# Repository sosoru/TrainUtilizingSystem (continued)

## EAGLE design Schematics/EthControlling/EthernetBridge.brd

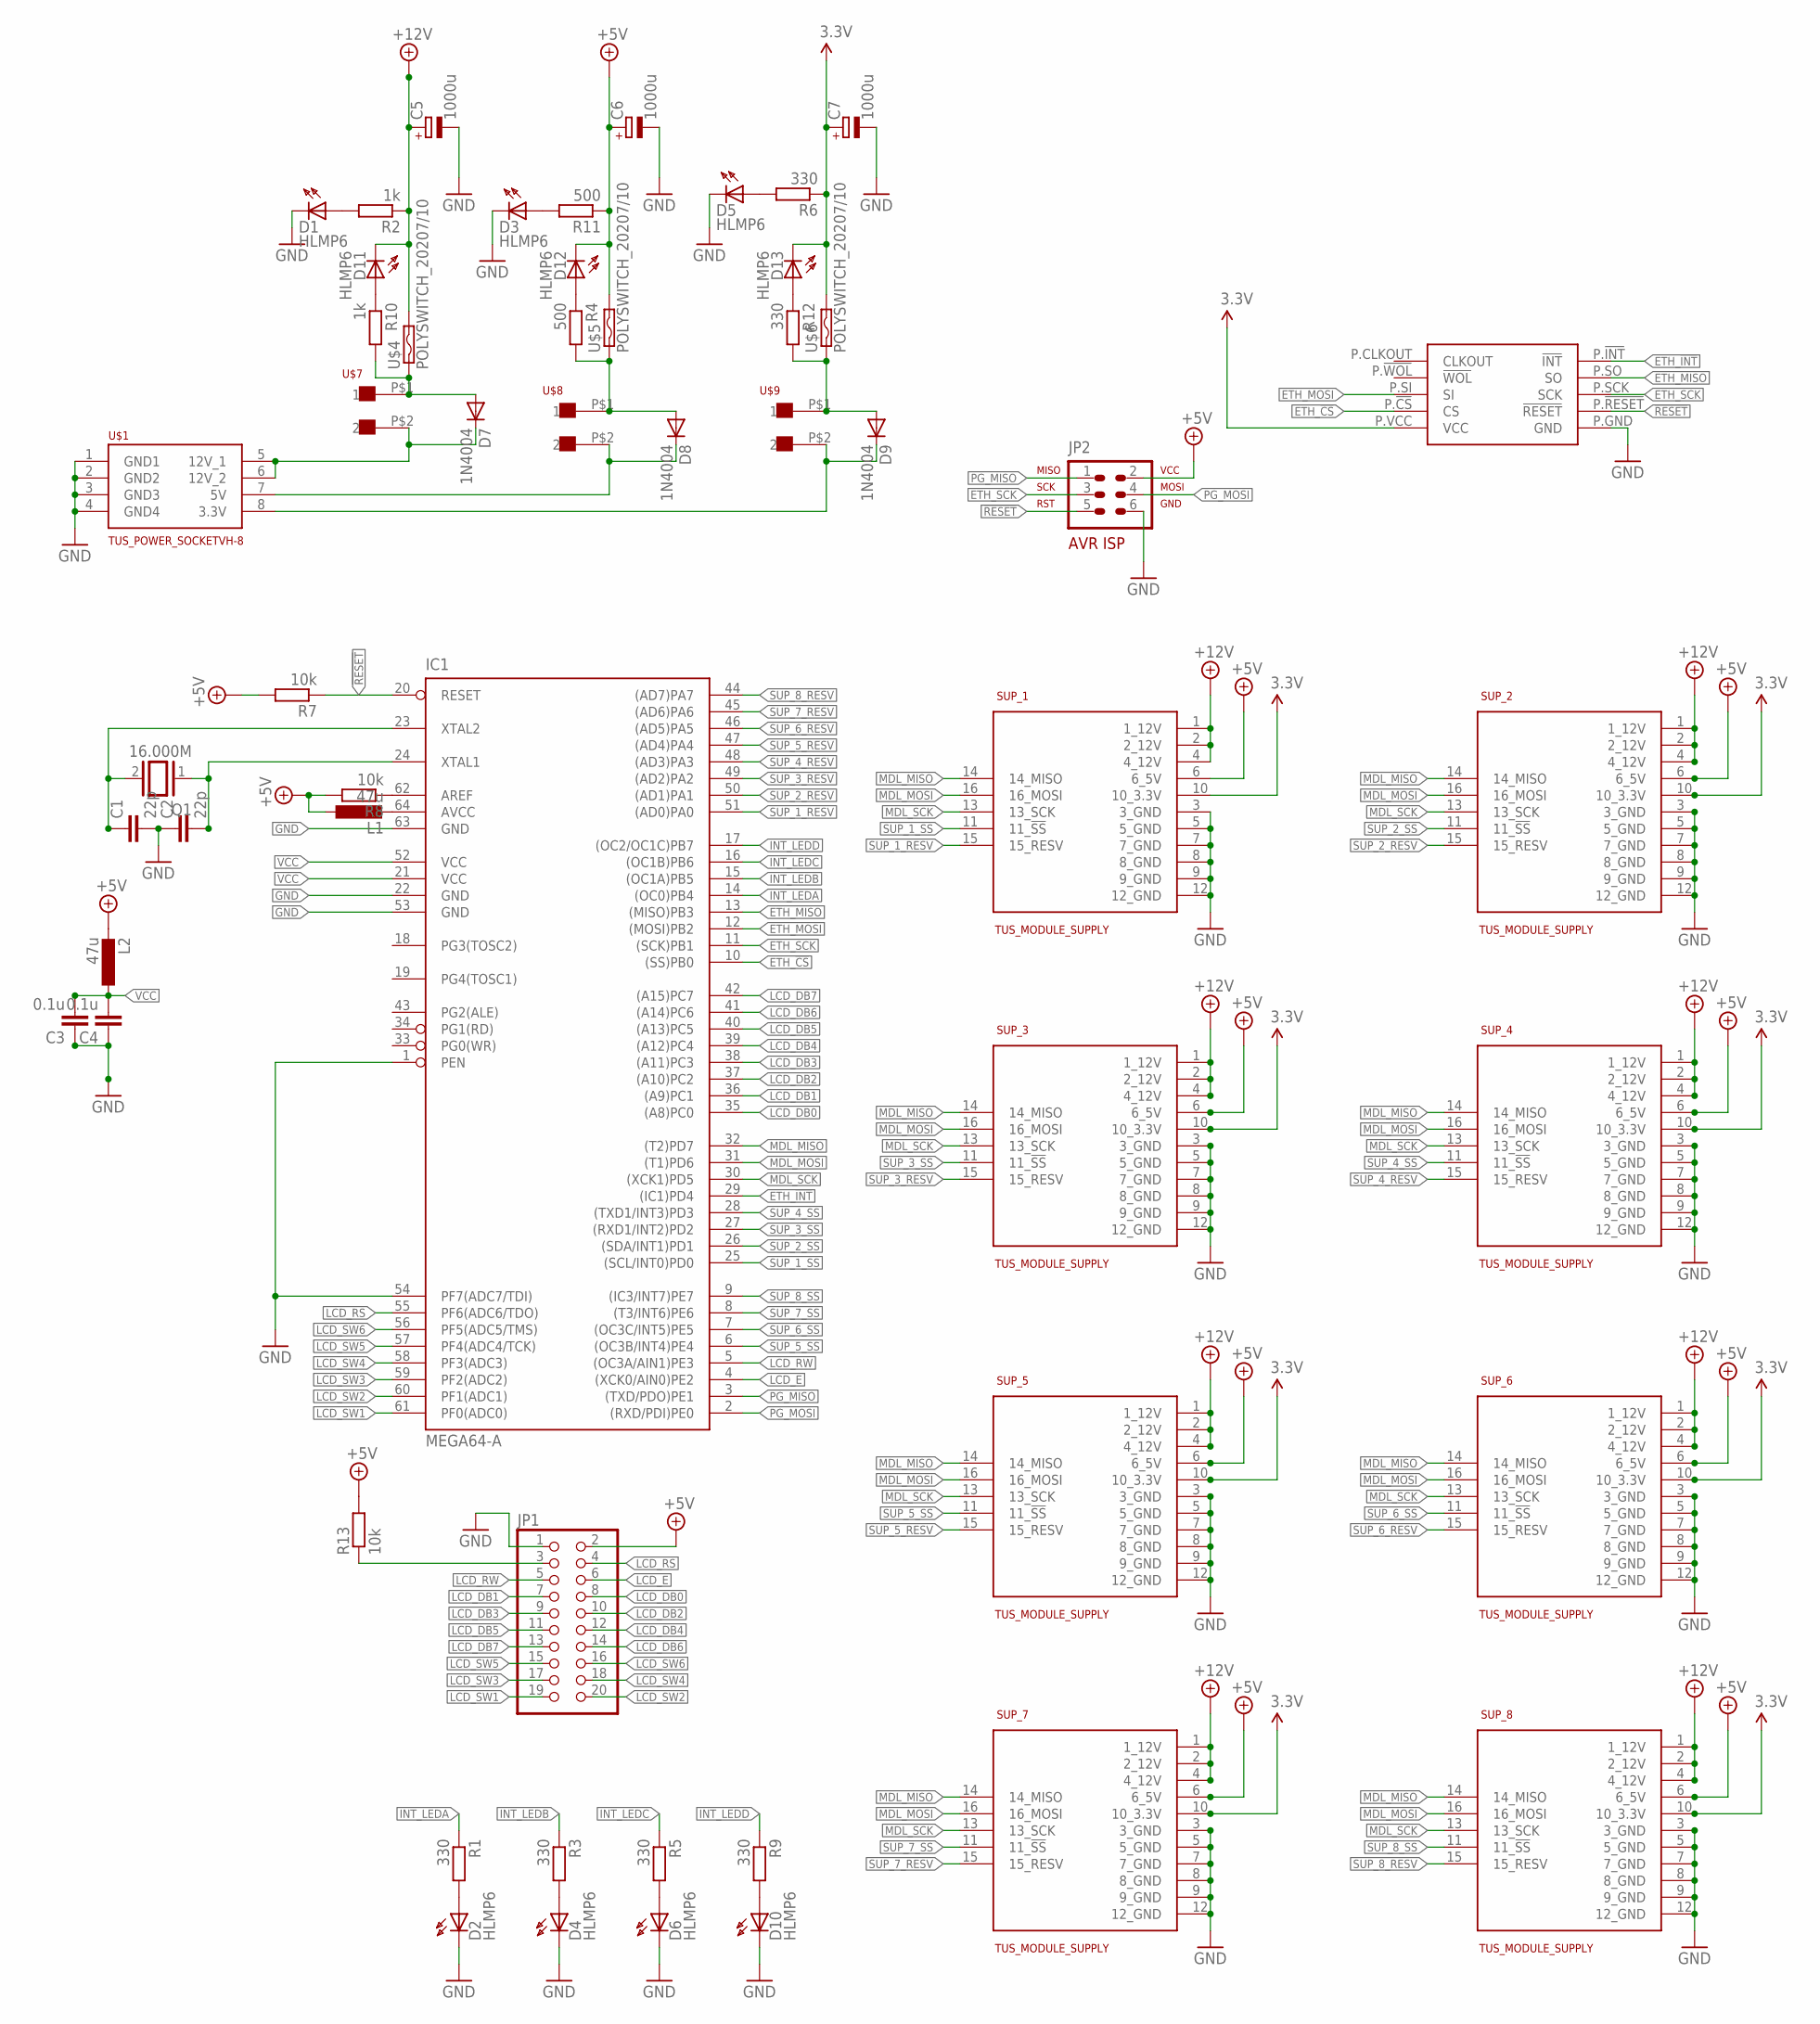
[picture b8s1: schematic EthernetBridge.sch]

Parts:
C1, C2: 22p; C2.5-3
C3, C4: 0.1u; C2.5-3
C5, C6, C7: 1000u; E5-10,5
D1, D2, D3, D4, D5, D6, D10, D11, D12, D13: HLMP6
D7, D8, D9: 1N4004; DO41-10
IC1: MEGA64-A; TQFP64
JP1: PINHD-2X10; 2X10
JP2: AVR-ISP-6VERT; AVR-ISP-6
L1, L2: 47u; 0204/7
Q1: 16.000M; QS
R1, R3, R5, R6, R9, R12: 330; 0204/7
R2, R10: 1k; 0204/7
R4, R11: 500; 0204/7
R7, R8, R13: 10k; 0204/7
SUP_1, SUP_2, SUP_3, SUP_4, SUP_5, SUP_6, SUP_7, SUP_8: TUS_MODULE_SUPPLY; 2X08
U$1: TUS_POWER_SOCKETVH-8; VH_8
U$2: AITENDO_ENC28J60
U$4, U$5, U$6: POLYSWITCH_20207/10; 0207/10
U$7, U$8, U$9: VH-2

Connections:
3.3V: C7.+, D13.K, R6.1, SUP_1.10 (10_3.3V), SUP_2.10 (10_3.3V), SUP_3.10 (10_3.3V), SUP_4.10 (10_3.3V), SUP_5.10 (10_3.3V), SUP_6.10 (10_3.3V), SUP_7.10 (10_3.3V), SUP_8.10 (10_3.3V), U$2.P.VCC (VCC), U$6.2
!RESET: IC1.20 (RESET), JP2.5, R7.1, U$2.P.!RESET (!RESET)
+5V: C6.+, D12.K, JP1.2, JP2.2, L1.1, L2.2, R7.2, R8.2, R11.1, R13.2, SUP_1.6 (6_5V), SUP_2.6 (6_5V), SUP_3.6 (6_5V), SUP_4.6 (6_5V), SUP_5.6 (6_5V), SUP_6.6 (6_5V), SUP_7.6 (6_5V), SUP_8.6 (6_5V), U$5.2
+12V: C5.+, D11.K, R2.1, SUP_1.1 (1_12V), SUP_1.2 (2_12V), SUP_1.4 (4_12V), SUP_2.1 (1_12V), SUP_2.2 (2_12V), SUP_2.4 (4_12V), SUP_3.1 (1_12V), SUP_3.2 (2_12V), SUP_3.4 (4_12V), SUP_4.1 (1_12V), SUP_4.2 (2_12V), SUP_4.4 (4_12V), SUP_5.1 (1_12V), SUP_5.2 (2_12V), SUP_5.4 (4_12V), SUP_6.1 (1_12V), SUP_6.2 (2_12V), SUP_6.4 (4_12V), SUP_7.1 (1_12V), SUP_7.2 (2_12V), SUP_7.4 (4_12V), SUP_8.1 (1_12V), SUP_8.2 (2_12V), SUP_8.4 (4_12V), U$4.2
ETH_!CS: IC1.10 ((SS)PB0), U$2.P.!CS (CS)
ETH_!INT: IC1.29 ((IC1)PD4), U$2.P.!INT (!INT)
ETH_MISO: IC1.13 ((MISO)PB3), U$2.P.SO (SO)
ETH_MOSI: IC1.12 ((MOSI)PB2), U$2.P.SI (SI)
ETH_SCK: IC1.11 ((SCK)PB1), JP2.3, U$2.P.SCK (SCK)
GND: C1.2, C2.1, C3.1, C4.1, C5.-, C6.-, C7.-, D1.K, D2.K, D3.K, D4.K, D5.K, D6.K, D10.K, IC1.1 (PEN), IC1.22 (GND), IC1.53 (GND), IC1.54 (PF7(ADC7/TDI)), IC1.63 (GND), JP1.1, JP2.6, SUP_1.3 (3_GND), SUP_1.5 (5_GND), SUP_1.7 (7_GND), SUP_1.8 (8_GND), SUP_1.9 (9_GND), SUP_1.12 (12_GND), SUP_2.3 (3_GND), SUP_2.5 (5_GND), SUP_2.7 (7_GND), SUP_2.8 (8_GND), SUP_2.9 (9_GND), SUP_2.12 (12_GND), SUP_3.3 (3_GND), SUP_3.5 (5_GND), SUP_3.7 (7_GND), SUP_3.8 (8_GND), SUP_3.9 (9_GND), SUP_3.12 (12_GND), SUP_4.3 (3_GND), SUP_4.5 (5_GND), SUP_4.7 (7_GND), SUP_4.8 (8_GND), SUP_4.9 (9_GND), SUP_4.12 (12_GND), SUP_5.3 (3_GND), SUP_5.5 (5_GND), SUP_5.7 (7_GND), SUP_5.8 (8_GND), SUP_5.9 (9_GND), SUP_5.12 (12_GND), SUP_6.3 (3_GND), SUP_6.5 (5_GND), SUP_6.7 (7_GND), SUP_6.8 (8_GND), SUP_6.9 (9_GND), SUP_6.12 (12_GND), SUP_7.3 (3_GND), SUP_7.5 (5_GND), SUP_7.7 (7_GND), SUP_7.8 (8_GND), SUP_7.9 (9_GND), SUP_7.12 (12_GND), SUP_8.3 (3_GND), SUP_8.5 (5_GND), SUP_8.7 (7_GND), SUP_8.8 (8_GND), SUP_8.9 (9_GND), SUP_8.12 (12_GND), U$1.1 (GND1), U$1.2 (GND2), U$1.3 (GND3), U$1.4 (GND4), U$2.P.GND (GND)
INT_LEDA: IC1.14 ((OC0)PB4), R1.1
INT_LEDB: IC1.15 ((OC1A)PB5), R3.1
INT_LEDC: IC1.16 ((OC1B)PB6), R5.1
INT_LEDD: IC1.17 ((OC2/OC1C)PB7), R9.1
LCD_DB0: IC1.35 ((A8)PC0), JP1.8
LCD_DB1: IC1.36 ((A9)PC1), JP1.7
LCD_DB2: IC1.37 ((A10)PC2), JP1.10
LCD_DB3: IC1.38 ((A11)PC3), JP1.9
LCD_DB4: IC1.39 ((A12)PC4), JP1.12
LCD_DB5: IC1.40 ((A13)PC5), JP1.11
LCD_DB6: IC1.41 ((A14)PC6), JP1.14
LCD_DB7: IC1.42 ((A15)PC7), JP1.13
LCD_E: IC1.4 ((XCK0/AIN0)PE2), JP1.6
LCD_RS: IC1.55 (PF6(ADC6/TDO)), JP1.4
LCD_RW: IC1.5 ((OC3A/AIN1)PE3), JP1.5
LCD_SW1: IC1.61 (PF0(ADC0)), JP1.19
LCD_SW2: IC1.60 (PF1(ADC1)), JP1.20
LCD_SW3: IC1.59 (PF2(ADC2)), JP1.17
LCD_SW4: IC1.58 (PF3(ADC3)), JP1.18
LCD_SW5: IC1.57 (PF4(ADC4/TCK)), JP1.15
LCD_SW6: IC1.56 (PF5(ADC5/TMS)), JP1.16
LCD_VO: JP1.3, R13.1
MDL_MISO: IC1.32 ((T2)PD7), SUP_1.14 (14_MISO), SUP_2.14 (14_MISO), SUP_3.14 (14_MISO), SUP_4.14 (14_MISO), SUP_5.14 (14_MISO), SUP_6.14 (14_MISO), SUP_7.14 (14_MISO), SUP_8.14 (14_MISO)
MDL_MOSI: IC1.31 ((T1)PD6), SUP_1.16 (16_MOSI), SUP_2.16 (16_MOSI), SUP_3.16 (16_MOSI), SUP_4.16 (16_MOSI), SUP_5.16 (16_MOSI), SUP_6.16 (16_MOSI), SUP_7.16 (16_MOSI), SUP_8.16 (16_MOSI)
MDL_SCK: IC1.30 ((XCK1)PD5), SUP_1.13 (13_SCK), SUP_2.13 (13_SCK), SUP_3.13 (13_SCK), SUP_4.13 (13_SCK), SUP_5.13 (13_SCK), SUP_6.13 (13_SCK), SUP_7.13 (13_SCK), SUP_8.13 (13_SCK)
unnamed: IC1.64 (AVCC), L1.2
unnamed: D1.A, R2.2
unnamed: D2.A, R1.2
unnamed: D4.A, R3.2
unnamed: D8.A, R4.2, U$5.1, U$8.P$1 (1)
unnamed: D9.C, U$1.8 (3.3V), U$9.P$2 (2)
unnamed: D6.A, R5.2
unnamed: D5.A, R6.2
unnamed: C2.2, IC1.24 (XTAL1), Q1.1
unnamed: D10.A, R9.2
unnamed: C1.1, IC1.23 (XTAL2), Q1.2
unnamed: IC1.62 (AREF), R8.1
unnamed: D7.A, R10.2, U$4.1, U$7.P$1 (1)
unnamed: D11.A, R10.1
unnamed: D3.A, R11.2
unnamed: D12.A, R4.1
unnamed: D13.A, R12.1
unnamed: D9.A, R12.2, U$6.1, U$9.P$1 (1)
unnamed: D7.C, U$1.5 (12V_1), U$1.6 (12V_2), U$7.P$2 (2)
unnamed: D8.C, U$1.7 (5V), U$8.P$2 (2)
PG_MISO: IC1.3 ((TXD/PDO)PE1), JP2.1
PG_MOSI: IC1.2 ((RXD/PDI)PE0), JP2.4
SUP_1_RESV: IC1.51 ((AD0)PA0), SUP_1.15 (15_RESV)
SUP_1_SS: IC1.25 ((SCL/INT0)PD0), SUP_1.11 (11_!SS)
SUP_2_RESV: IC1.50 ((AD1)PA1), SUP_2.15 (15_RESV)
SUP_2_SS: IC1.26 ((SDA/INT1)PD1), SUP_2.11 (11_!SS)
SUP_3_RESV: IC1.49 ((AD2)PA2), SUP_3.15 (15_RESV)
SUP_3_SS: IC1.27 ((RXD1/INT2)PD2), SUP_3.11 (11_!SS)
SUP_4_RESV: IC1.48 ((AD3)PA3), SUP_4.15 (15_RESV)
SUP_4_SS: IC1.28 ((TXD1/INT3)PD3), SUP_4.11 (11_!SS)
SUP_5_RESV: IC1.47 ((AD4)PA4), SUP_5.15 (15_RESV)
SUP_5_SS: IC1.6 ((OC3B/INT4)PE4), SUP_5.11 (11_!SS)
SUP_6_RESV: IC1.46 ((AD5)PA5), SUP_6.15 (15_RESV)
SUP_6_SS: IC1.7 ((OC3C/INT5)PE5), SUP_6.11 (11_!SS)
SUP_7_RESV: IC1.45 ((AD6)PA6), SUP_7.15 (15_RESV)
SUP_7_SS: IC1.8 ((T3/INT6)PE6), SUP_7.11 (11_!SS)
SUP_8_RESV: IC1.44 ((AD7)PA7), SUP_8.15 (15_RESV)
SUP_8_SS: IC1.9 ((IC3/INT7)PE7), SUP_8.11 (11_!SS)
VCC: C3.2, C4.2, IC1.21 (VCC), IC1.52 (VCC), L2.1

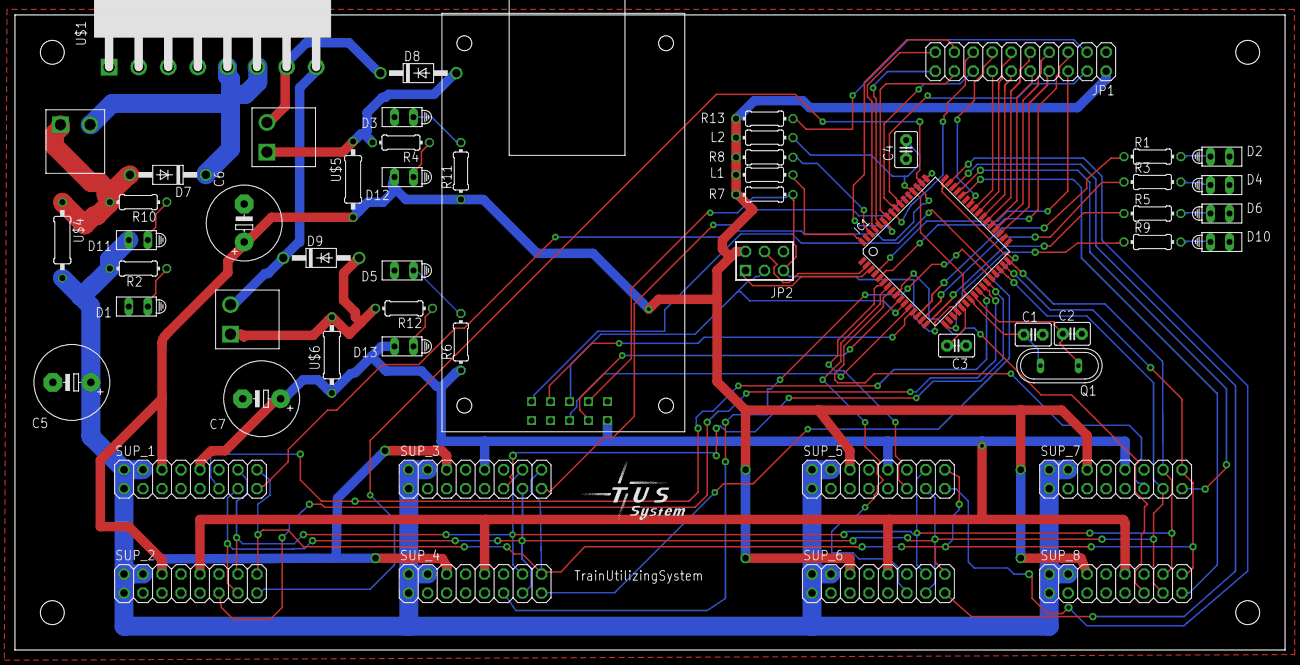
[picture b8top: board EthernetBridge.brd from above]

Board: 2 copper layers, 170.0 x 85.0 mm, 55 parts (0 on the bottom side), 74 nets.

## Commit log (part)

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2012-11-21 [autosave] TusSolution/DialogConsole/DialogConsole.cs
2012-11-21 [autosave] SensorLibrary/Packet/PacketIO/EthClient.cs
2012-11-21 [autosave] TestProject/TestProject.csproj
2012-11-21 [autosave] TestProject/RouteTest/UnitTest1.cs
2012-11-21 [autosave] TusSolution/DialogConsole/RouteGeneratorForTwelve.cs
2012-11-21 [autosave] TestProject/RouteTest/TwelveLayoutTest.cs
2012-11-21 [autosave] TusSolution/DialogConsole/DialogConsole.csproj
2012-11-21 [autosave] TusSolution/RouteLibrary/Base/Route.cs
2012-11-22 [autosave] TusSolution/RouteLibrary/Base/DeviceEffector.cs
2012-11-22 [autosave] TusSolution/RouteLibrary/Base/BlockSheet.cs
2012-11-22 [autosave] TusSolution/RouteLibrary/Base/Vehicle.cs
2012-11-23 [autosave] TestProject/RouteTest/StaLoopTest.cs
2012-11-23 [autosave] TestProject/EthClientTest.cs
2012-11-24 [autosave] SensorLibrary/Packet/PacketDatas/PacketBasis.cs
2012-11-24 [autosave] SensorLibrary/Packet/PacketControl/PacketServer.cs
2012-11-24 [autosave] TusSolution/DengoController/Program.cs
2012-11-24 [autosave] TusSolution/DengoController/DengoController.csproj
2012-11-27 [autosave] TusSolution/TusSolution.sln
2012-11-28 published for festival at 12/11/28
2012-11-28 [autosave] TestProject/app.config
2012-11-28 [autosave] TusSolution/DialogConsole/App.config
2012-11-28 [autosave] TusSolution/RouteLibrary/RouteLibrary.csproj
2012-11-30 [autosave] SensorLibrary/Packet/PacketIO/TusEthernetIO.cs
2012-12-01 [autosave] SensorLibrary/SensorLibrary.csproj
2012-12-23 [autosave] TestProject/ConsoleTest/SheetFactoryTest.cs
2012-12-23 [autosave] TusSolution/DialogConsole/Factory/SheetFactory.cs
2012-12-24 [autosave] TusSolution/DialogConsole/Factory/ServerFactory.cs
2012-12-25 [autosave] TusSolution/DialogConsole/Properties/Settings.settings
2012-12-25 [autosave] TusSolution/DialogConsole/Factory/DeviceDefinitionFactory.cs
2012-12-25 [autosave] TusSolution/DialogConsole/Factory/DeviceControllerFactory.cs
2012-12-25 [autosave] TestProject/ConsoleTest/Composition/SheetFactoryTest.cs
2012-12-25 [autosave] TusSolution/DialogConsole/Properties/AssemblyInfo.cs
2012-12-25 [autosave] TusSolution/DialogConsole/Settings.cs
2012-12-27 [autosave] TusSolution/DialogConsole/Properties/Settings.Designer.cs
2012-12-27 [autosave] TusSolution/DialogConsole/Factory/IConsoleApplicationSettings.cs
2012-12-27 refactoring DialogConsole (init)
2012-12-28 re-place projectfiles
2012-12-28 ditto
2012-12-29 extract Device classes and its factories to the new project : using MEF for factory classes
2012-12-29 sample files accessible as relative path
2012-12-30 fix tests to make a successful result
2012-12-30 Extract device communicating layer and device specificating layer from SensorLibrary to Tus.Communicate projects; delete SensorLibrary
2012-12-30 Rename RouteLibrary to Tus.Route
2013-01-01 Extract factories
2013-01-07 Extract properties fromDialogConsole; fix Factory tests
2013-01-07 Extract methods in DialogConsole to the externel classes that impls IFeature; composing classes is delegated to MEF
2013-01-07 fix misspell
2013-01-10 properly setuped deploying test project
2013-01-16 Extract a feature of serving state information as json format
2013-02-15 fix a bug that commands sending to devices is delaying
2013-03-26 setting for 634 layout
2013-03-26 setting ofr 0327 layout test
2013-03-31 impl RouteYamlParser
2013-03-31 Rename RouteParser -> RouteLiteralParser
2013-04-02 change namespace Tus.Route to Tus.TransControl
2013-04-02 impl route definition file parser and test it
2013-04-06 閉塞極性の考慮とコンソールUIの改善．route inputのrevオプションを無効
2013-04-10 many vehicles に対応
2013-04-22 impl some attributes to MotorState, Motor, SwitchState, Switch for handling by serializer, and test them
2013-04-22 ditto. impl to SensorState, Sensor, and test them. and impl set methods to voltage properties of SensorState, and test them
2013-04-23 add DeploymentItem attributes for supecifing sample files to test classes
2013-04-23 refactoring DeviceControllers
2013-04-26 SwitchPage refactoring
2013-04-27 impl SwitchPage
2013-04-29 refactoring CnosolePage, add Vehicle, Motor, Switch Pages and test them
2013-05-02 make BlockPage and some web interfaces
2013-05-02 impl ignoring unconnected devices when transmiting on EhternetBridge
2013-05-04 edit some code for layout test
2013-05-12 rename test project
2013-05-13 Vehicle側で編成長を動的に設定するように変更
2013-05-15 coding layout now
2013-05-21 refactoring Route
2013-05-23 refactoring route classes and test them
2013-05-24 実機テストdone VehicleのStop時にはControlBlockを先頭とするようにAllocateし直せばよい？
2013-05-31 misc changes
2013-06-28 pass tests
2013-07-06 more stable manipulation
2013-08-01 MotorDataにCurrentMemoryを追加
2013-08-09 閉塞チェックできたはず
2013-08-16 0816 stable
2013-08-16 trivial changes
2014-10-03 2014/10/04 NS exhibition (blockage feature works successfully)
2014-10-11 Add new board AtxPowerDispatcher3 and some libraries
2014-10-11 Add new method HaltHere, LeaveHere on class Vehicle. Haltableブロックのみをロックすることで，閉塞を他のVehicleに渡せる．追い越しサポートのため
2014-10-13 Add loging feature on TusSolution. ログ機能を追加，関連ライブラリでConsole.WriteLineしてるところを変更． マルチディスプレイだと表示に難点
2014-10-13 Submit AtxPowerDispatcher3
2014-10-13 Add resuming last vehicles feature 最後に終了した状態に復帰する機能を追加
2015-11-19 add AutoController Project
2015-11-19 fix conflicts
2015-11-19 add lacked file while merging
2015-11-19 Blockをシリアライズする際，Deviceの情報が冗長になることがある．シリアライズ用のクラスBlockSendingObjectを定義して，VehicleとRoute等々をシリアライズする際，そっちを返すようにした
2015-11-20 DevicePacket，EthPacketのサイズを増加，データ領域を拡大することで，パケット分割の抑止，オーバヘッドを抑える． これに伴いデバイス側のコードも変更．コード依存のトラブルがあるかもしれない．
    ・Tus.CommunicationのStructLayoutサイズを変更
    ・EthernetBridgePpはATmega128AのSRAMが足らないので，PacketDispatcherのバッファ等を変更
    ・ARPバッファとENC28J60から引っ張る際のバッファサイズを変更
    ・AtmelStudio7相当にプロジェクトファイルをアップデート
2015-11-20 DialogConsoleの基板間通信インターバルを変更
2015-11-20 AutoControllerのデバッグ
    ・現在位置の追加
    ・列車指定のコンボボックス周りの処理
    ・Phaseタブページの位置からスタートするよう変更
2015-11-20 MotorBoardで現在の状態をpackするところ、パケット分割していたのを消去
2015-11-20 trivial edit
2015-11-20 バッファ数の調整
2015-11-20 DeviceChunckの実装
2015-11-20 DevicePacketのパケットサイズの調整
    ・あまり大きすぎると，基板側のバッファが間に合わず，通信が出来ない
    ・小さすぎると，オーバーヘッドになるのでうまい調整が必要
2015-11-20 commit changed files for merge
2015-11-20 Revert "DialogConsoleの基板間通信インターバルを変更"
    This reverts commit cce4b3bcaaf4426d47854d4190d95408c621826f.
2015-11-20 Revert "DevicePacket，EthPacketのサイズを増加，データ領域を拡大することで，パケット分割の抑止，オーバヘッドを抑える．"
    This reverts commit 25e1c792e467d24b6b1e54d99712ab3d4d0bdeb5.
2015-11-24 AutoControllerで待機する閉塞数を設定出るようにした
    ・StayDistanceの追加
    ・Untenクラスで，StayDistanceとVehicle.Distanceを比較して，Phaseの進行を待機するように変更
2015-11-27 Revert "DevicePacketのパケットサイズの調整"
    This reverts commit 24cd721e900ec5d5549a4b02af50fcce498a80b5.
    Conflicts:
    DeviceSoftware/TusDevice/EthernetBridgePp/tus_mst/tus_mstcfg.hpp
    DeviceSoftware/TusDevice/libtus/packet.h
    ServerUtility/TusSolution/Tus.Communication/DevicePacket.cs
    ServerUtility/TusSolution/Tus.Communication/Ethernet/EthPacket.cs
2015-11-27 Revert "DeviceChunckの実装"
    This reverts commit 8cc489ddc1e2e57ec87ac8a6e8629e372b61f016.
2015-11-27 Revert "バッファ数の調整"
    This reverts commit b1aec50cd7cf9e136eeaa3588d1a4f891f35e9a4.
    Conflicts:
    DeviceSoftware/TusDevice/EthernetBridgePp/EthConfig.hpp
    DeviceSoftware/TusDevice/EthernetBridgePp/EthernetBridgePp_6_1.cppproj
    DeviceSoftware/TusDevice/EthernetBridgePp/tus_mst/tus_mstcfg.hpp
    DeviceSoftware/TusDevice/libtus/libtus_6_1.cproj
2015-11-27 Revert "MotorBoardで現在の状態をpackするところ、パケット分割していたのを消去"
    This reverts commit 153ce6e8aee79e08d63e82e37f2f13b1b50b55cd.
2015-11-27 EhernetBoardのLCD機能の削除
    ・DialogConsoleにマニフェストの追加
2015-12-12 モータコントローラのソフト修正
    ・WaitingPulseモードで，同じ基板の他の内部モジュールに命令をディスパッチする判定条件が間違っていた
    （おそらくエンディアンに関する修正を行ったときに巻き込まれた？）
    ・avr-gcc系の古いToolchainに関する設定を追加
    （c++系のフレームワークでwarningが出ていたため対応）
2016-03-18 TUSEthernetIOのポート番号指定を変更
2016-03-22 引き継ぎで動いたやつ
2016-03-28 テストケースの更新 デバイス側ソフトのビルドオプションの変更（avr-g++のオプション-mrelaxの有無で挙動が変化する？） ExtractPackedPacketで長さ不正なパケットの場合にはyield breakするようにした
